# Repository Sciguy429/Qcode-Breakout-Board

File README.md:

# Qcode-Breakout-Board

**UPDATE:** As of 10-13-2023 I have recived my first prototype PCB's from JLPCB. They look good so far, but I will need to assemble and test them out for sure. More updates soon.

This is an in-progress project that attempts to re add Qcode displays to lower end Asus motherboards. Asus has chosen to only provide this feature on its extremely high end boards, which now cost significantly more than they used too. This project started out as a breadboard proof of concept posted to [Reddit](https://www.reddit.com/r/techsupportmacgyver/comments/16v3af7/asus_removed_qcode_displays_from_low_end/) and gained a decent bit of traction. This repository aims to archive all of the work I have done to make this thing a reality. Do keep in mind, I am a hobbyist, not a professional PCB designer. I take no responsibility if you choose to replicate my work and end up frying your motherboard, or worse.

# How it all works
Still here? Cool lets go...

Part of what confused me the most about all of this was just how easy it was to set up. It all started when I purchased a new x570 board to replace my aging Crosshair Vii. The new board of course did not come with a Qcode display but while I was installing it into my case I noticed a weird header on the bottom, the same size as an Arduino ICSP header, labeled 'COM_DEBUG'. I am far to curious for my own good so of course I googled it once my PC was up and running again a few hours later. I found a few differing sites that had references to the thing, a post on the [LTT forums](https://linustechtips.com/topic/1373425-phd-6000-connector-on-asus-mb-what-i-fond/) had the most information, including a pinout found in an official Asus manual. Oddly enough nobody on the forum had done any further testing with there own boards.

The connector pinout in question looks like this:

There are quite literally only two pins to try here, and the name 'COM_DEBUG' implies serial to me. So I hooked up a cheap USB to UART to both of them and turns out that the bottom left pin (SOUTC_P80) just dumps out post codes as single bytes at 115200 baud. No weird formatting, no weird speeds, it just dumps em out. (The other pin appears to be something else, whatever protocol it is using, it is not normal serial. I was unable to read anything out of it.)

This kinda floored me, as I quickly realized that it would be trivial to make a cheap MCU read in those bits and put them up onto some 7-segment displays. I then built the original breadboard prototype that is seen in the Reddit post, using some old code from a clock I made years ago to drive the two displays.

# PCB's
Next up was making some PCB's and I currently have two prototype designs.

The first is a one to one clone of the breadboard circuit, using two generic 7-segment displays and a relatively compact board layout.

The second is a much improved version, adding an additional 4 displays driven off of the ADC pins for more potential functionality. This board is much larger though, and more expensive to manufacture.

Prototypes of both of these boards are currently on order from JLPCB and should arrive within a month or so. Anyone interested in them is more than welcome to have their own boards manufactured. I had originally setup tolerances to allow for PCB milling (I have a little engraving machine) but I gave up on this once I created the 3X version. The tolerances are still set though, both designs should be millable, though you will need a nicer mill than I have.

Both designs use a 2x3 pin header for the COM_DEBUG port as well as have a single 1x2 header next to it for use with dupont jumpers. The header is the same size as an Arduino ICSP header and the ribbon cables for them do fit (The header on the board is missing a pin but that dose not prevent the cable from attaching). It is also theoretically possible to solder a female 2x3 header to the backside of the board and plug it directly in, though you will need some good luck with your clearances.

Unfortunately, the COM_DEBUG header dose not provide a +5V on it. It has a +3.3V pin, but no +5V power. As such in order to power the Arduino Mini an auxiliary source of +5V is needed. To the left side of the MCU a header has been provided for this. You can wire up the +5V pin directly to a +5V source, I am using a USB2 header myself, or you can connect the RAW pin to any voltage between +7V-12V (a fan header for instance). The USB2 header has the nice side effect for me of turning the display off when my PC is in hard off power states but not while it is sleeping.

# Firmware
Currently only preliminary firmware is available. This code only works on the 1X board variant and it nearly identical to what was running on the bread board prototype. It is a fairly simple affair that just spends the entire main loop checking for new POST code data and has a 100hz interrupt driving the multiplexed displays. This firmware is likely fine for 98% of potential users though and will likely remain as the only firmware amiable for the simple 1X board.

As for the 3X board, I intend to add a proper settings menu to it using the extra display real estate among other things. By default the displays will likely 'scroll' though the last three codes received, giving you easy access to more than just one of the POST codes your motherboard has sent. It may even be possible to store basic descriptions of the codes and display them on the screens, though that is likely exiting the scope of what a single Atmel-368p can do on it's own.

# Future plans
Someone mentioned something interesting to me on the Reddit post. They were wondering if an ESP32 could plug into the motherboard and send the codes to a phone. This got my attention as ESP32's use +3.3V power, which is already being provided right on the COM_DEBUG connector. I found one for fairly cheep and ordered it, along with a compatible TFT LCD screen. There are a few cool possibilities for this.

It would be pretty easy to design a small board that accepts a cheap ESP32 module and plugs right into the motherboard, supplying both power and serial data to the ESP32. You could then connect to it with a mobile device and have easy access to POST data, all at an extremely cheap cost.

The other idea that I am interested in involves that TFT LCD. The 8-bit MCU in an Arduino simply can't do graphics, but an ESP32 certainly can. It shouldn't be that hard to hook one up to a cheap TFT LCD on a board somewhere between the size as the 1X and 3X. With an LCD the possibilities for the firmware are endless. An ESP32 would be capable of storing thousands of past codes in history and likely a complete lexicon of code descriptions easily displayed on the TFT LCD screen.

# So, are you going to sell it?
Honestly, I am not sure...

I have never sold a PCB project like this before. The base parts for the 1X and even the 3X boards bearly even add up to $10 on Aliexpress. I built the prototype with random stuff that I just had on hand. If there is a solid interest in people who want to buy one, I might consider it, but as of now I want to wait and see.

# Disclaimer
Neither my self or this project is associated with Asus or AsusTEK in any way shape or form. I am an independent hobbiest.

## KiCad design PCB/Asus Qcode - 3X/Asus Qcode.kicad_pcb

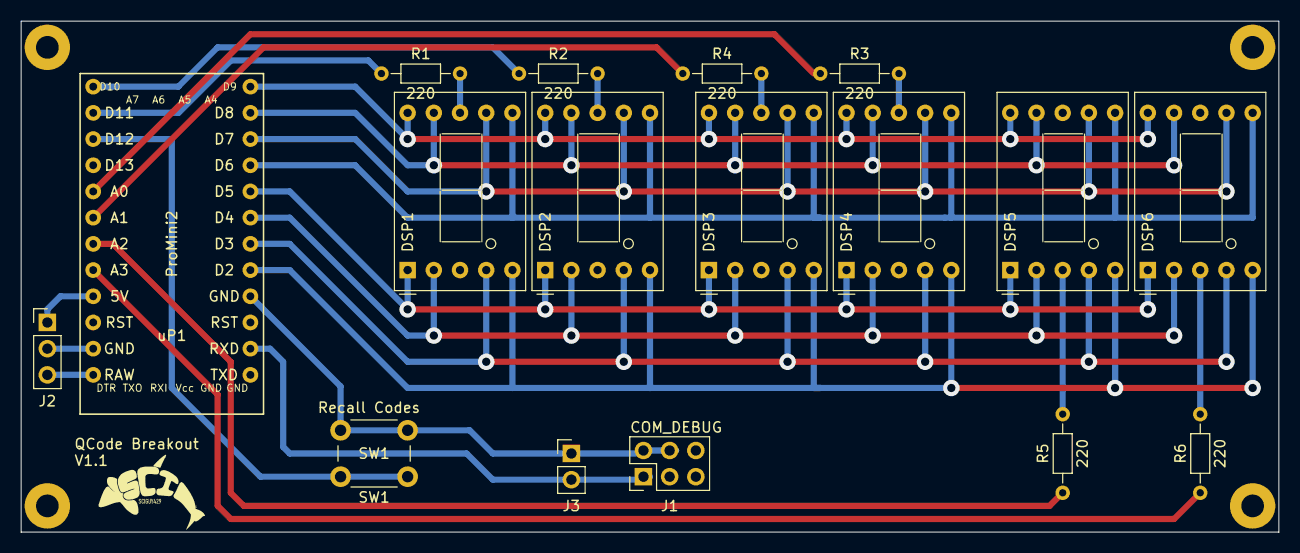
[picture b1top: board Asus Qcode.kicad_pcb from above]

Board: 2 copper layers, 121.9 x 49.5 mm, 17 parts (0 on the bottom side), 26 nets.

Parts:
DSP1, DSP2, DSP3, DSP4, DSP5, DSP6: LTS-6960HR; D1X8K
J1: COM_DEBUG; PinHeader_2x03_P2.54mm_Vertical
J2: Conn_01x03_Pin; PinHeader_1x03_P2.54mm_Vertical
J3: Conn_01x02_Pin; PinHeader_1x02_P2.54mm_Vertical
R1, R2, R3, R4, R5, R6: 220; R_Axial_DIN0204_L3.6mm_D1.6mm_P7.62mm_Horizontal
SW1: Recall Codes; SW_PUSH_6mm_H5mm
uP1: ProMini2; Pro_Mini_EDIT

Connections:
/a: DSP1.7 (a), DSP2.7 (a), DSP3.7 (a), DSP4.7 (a), DSP5.7 (a), DSP6.7 (a), uP1.16 (PD7)
/b: DSP1.6 (b), DSP2.6 (b), DSP3.6 (b), DSP4.6 (b), DSP5.6 (b), DSP6.6 (b), uP1.15 (PD6)
/c: DSP1.4 (c), DSP2.4 (c), DSP3.4 (c), DSP4.4 (c), DSP5.4 (c), DSP6.4 (c), uP1.12 (PD3)
/d: DSP1.2 (d), DSP2.2 (d), DSP3.2 (d), DSP4.2 (d), DSP5.2 (d), DSP6.2 (d), uP1.13 (PD4)
/dp: DSP1.5 (DP), DSP2.5 (DP), DSP3.5 (DP), DSP4.5 (DP), DSP5.5 (DP), DSP6.5 (DP), uP1.11 (PD2)
/dsp1: DSP1.8 (C.A.), R1.2
/dsp2: DSP2.8 (C.A.), R2.2
/dsp3: DSP3.8 (C.A.), R4.2
/dsp4: DSP4.8 (C.A.), R3.2
/dsp5: DSP5.3 (C.A.), R5.2
/dsp6: DSP6.3 (C.A.), R6.2
/e: DSP1.1 (e), DSP2.1 (e), DSP3.1 (e), DSP4.1 (e), DSP5.1 (e), DSP6.1 (e), uP1.14 (PD5)
/f: DSP1.9 (f), DSP2.9 (f), DSP3.9 (f), DSP4.9 (f), DSP5.9 (f), DSP6.9 (f), uP1.17 (PB0)
/g: DSP1.10 (g), DSP2.10 (g), DSP3.10 (g), DSP4.10 (g), DSP5.10 (g), DSP6.10 (g), uP1.18 (PB1)
GND: J1.2 (GND), J1.4 (GND), J3.1, SW1.2, uP1.10 (GND)
unnamed: J1.1 (SOUTC_P80), J3.2, uP1.8 (RX_D0)
unnamed: J2.1, uP1.22 (Vcc/5v)
unnamed: J2.2, uP1.20 (GND)
unnamed: J2.3, uP1.19 (RAW)
unnamed: R2.1, uP1.30 (PB2)
unnamed: R1.1, uP1.29 (PB3)
unnamed: SW1.1, uP1.28 (PB4)
unnamed: R3.1, uP1.26 (PC0/A0)
unnamed: R4.1, uP1.25 (PC1/A1)
unnamed: R5.1, uP1.24 (PC2/A2)
unnamed: R6.1, uP1.23 (PC3/A3)

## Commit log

2023-09-30 Add Kicad designs
2023-09-30 Remove logo files
2023-09-30 Add basic firmware
2023-09-30 Fix PCB routing issues
2023-09-30 More PCB fixes
2023-09-30 Even more tweaks to the PCB
2023-09-30 More PCB Tweaks
2023-10-02 Update PCB files
2023-10-02 Upload screenshots
2023-10-02 Add more images
2023-10-02 Fix spelling errors
2023-10-05 Slight 1X firmware tweaks
2023-10-05 Final PCB tweaks for JLPCB order
